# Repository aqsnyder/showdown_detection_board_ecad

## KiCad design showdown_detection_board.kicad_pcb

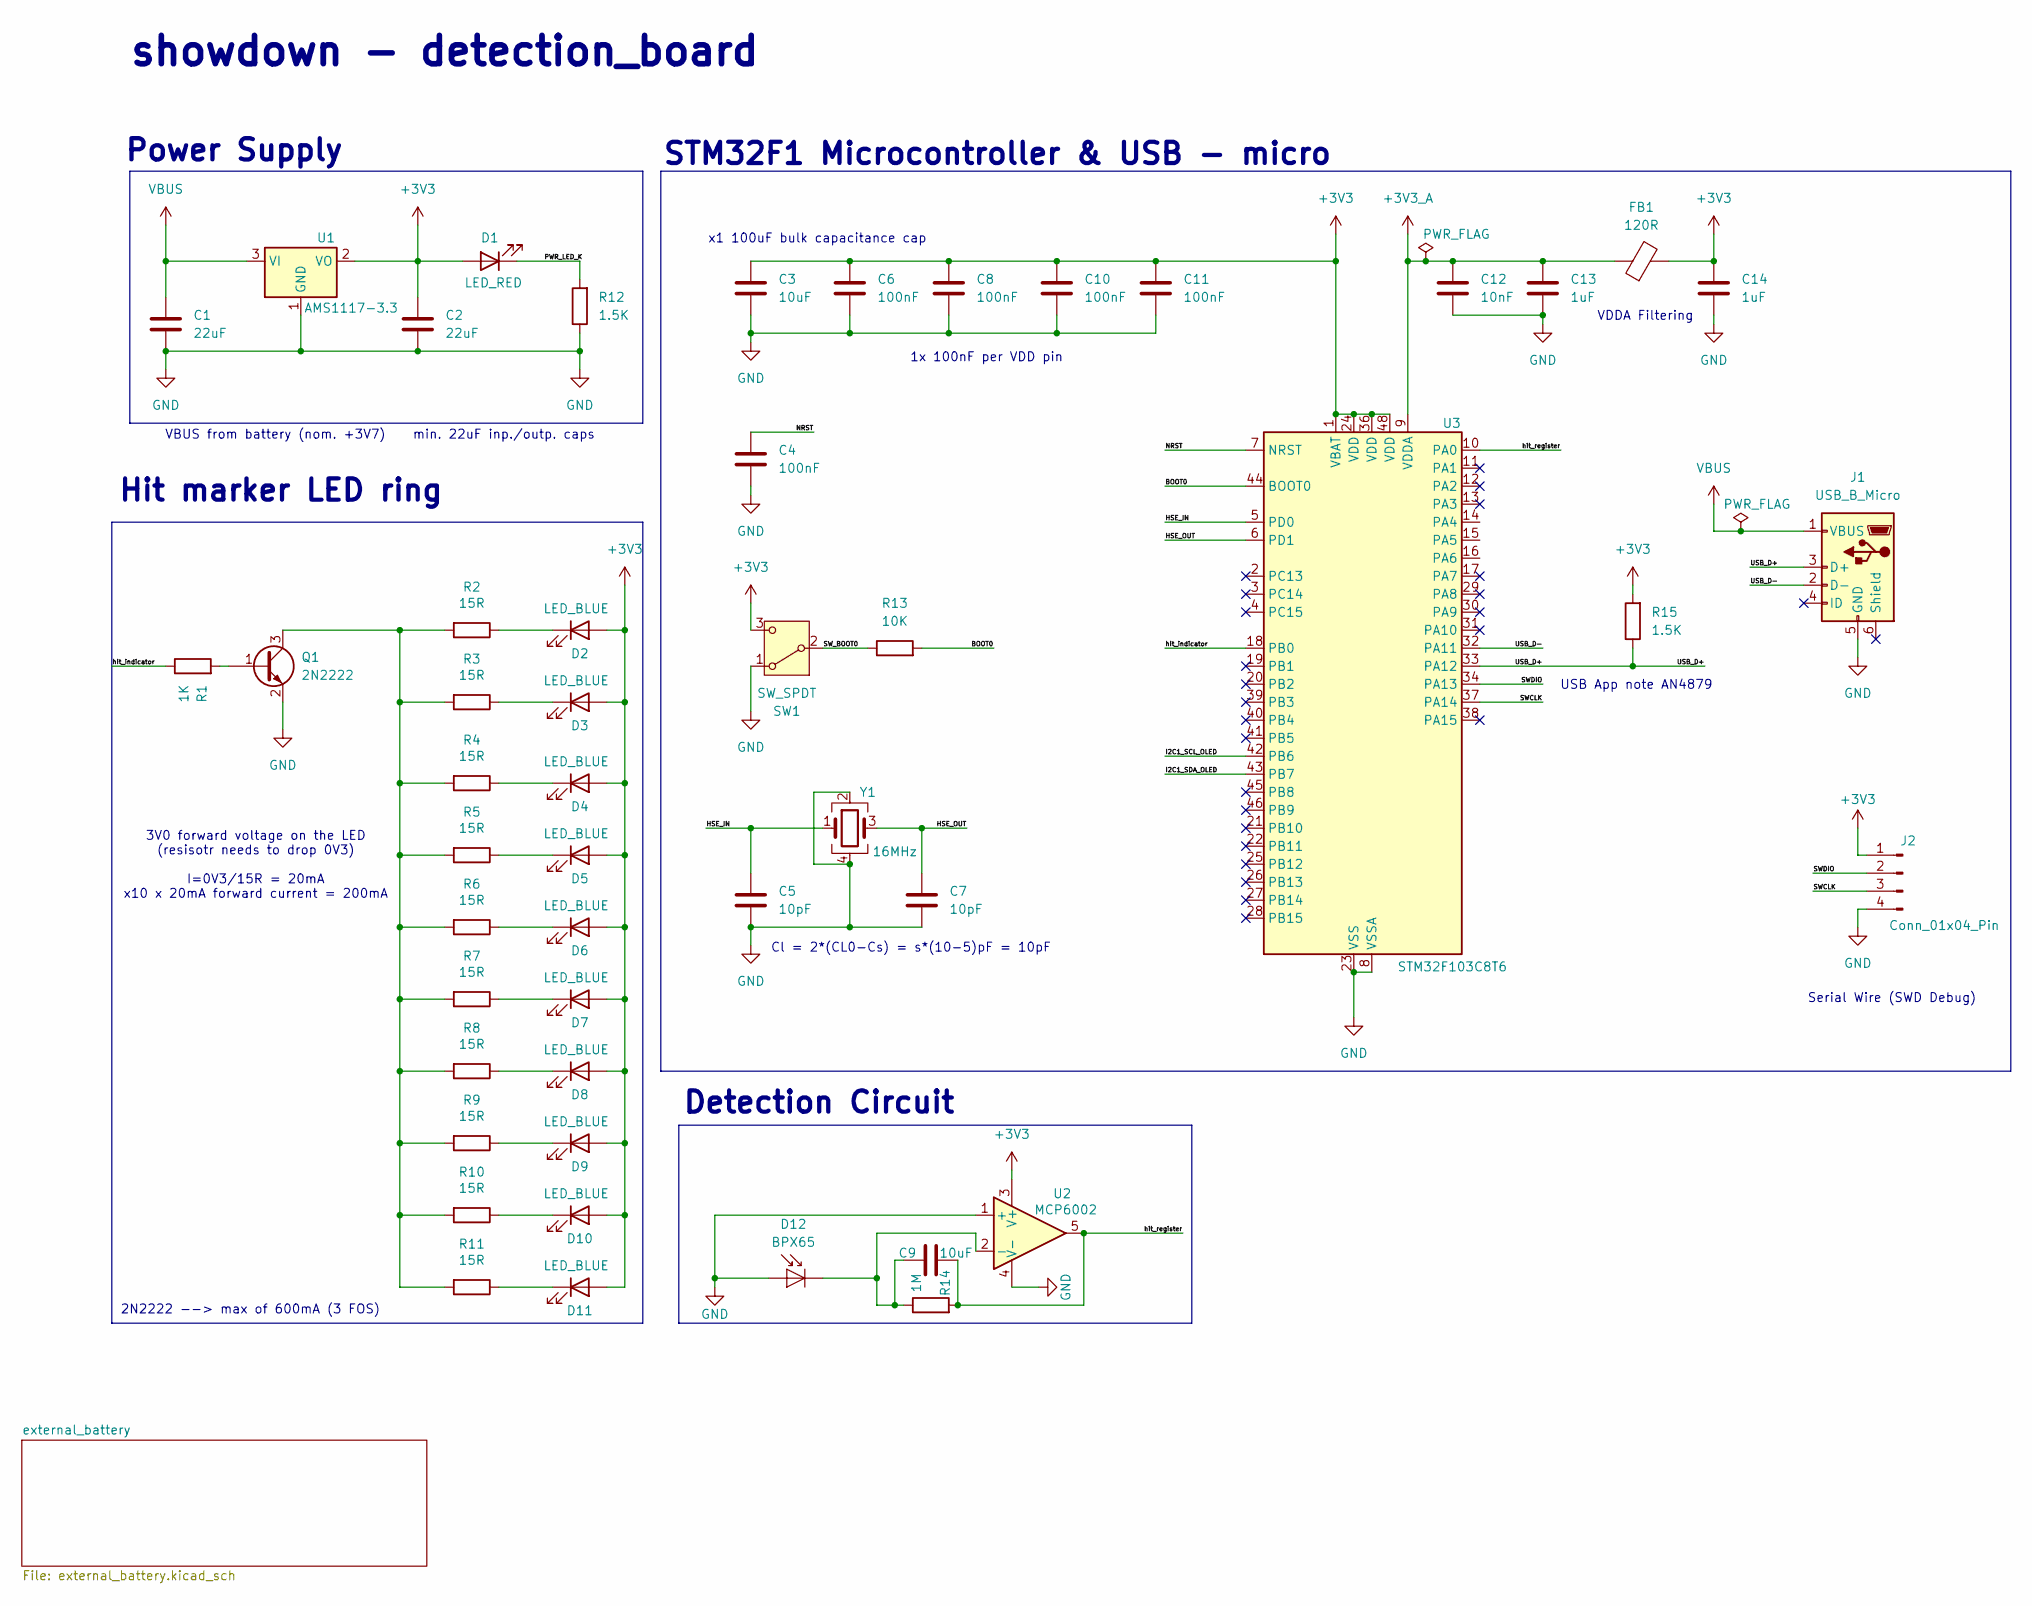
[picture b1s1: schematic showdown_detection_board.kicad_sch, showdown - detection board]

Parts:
C1, C2: 22uF; C_0603_1608Metric
C3, C9: 10uF; C_0603_1608Metric
C4, C6, C8, C10, C11: 100nF; C_0603_1608Metric
C5, C7: 10pF; C_0603_1608Metric
C12: 10nF; C_0603_1608Metric
C13, C14: 1uF; C_0603_1608Metric
D1: LED_RED; LED_0805_2012Metric
D2, D3, D4, D5, D6, D7, D8, D9, D10, D11: LED_BLUE; LED_0805_2012Metric
D12: BPX65; TO-18-2_Lens
FB1: 120R; L_0603_1608Metric
J1: USB_B_Micro; USB_Micro-AB_Molex_47590-0001
J2: Conn_01x04_Pin; PinHeader_1x04_P2.54mm_Horizontal
Q1: 2N2222; TO-92
R1: 1K; R_0603_1608Metric
R2, R3, R4, R5, R6, R7, R8, R9, R10, R11: 15R; R_0603_1608Metric
R12, R15: 1.5K; R_0603_1608Metric
R13: 10K; R_0603_1608Metric
R14: 1M; R_0603_1608Metric
SW1: SW_SPDT; SW_Slide-03_Wuerth-WS-SLTV_10x2.5x6.4_P2.54mm
U1: AMS1117-3.3; SOT-223-3_TabPin2
U2: MCP6002; TDFN-8-1EP_3x2mm_P0.5mm_EP1.3x1.4mm
U3: STM32F103C8T6; LQFP-48_7x7mm_P0.5mm
Y1: 16MHz; Crystal_SMD_3225-4Pin_3.2x2.5mm

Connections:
+3V3: C2.1, C3.1, C6.1, C8.1, C10.1, C11.1, C14.1, D1.2 (A), D2.2 (A), D3.2 (A), D4.2 (A), D5.2 (A), D6.2 (A), D7.2 (A), D8.2 (A), D9.2 (A), D10.2 (A), D11.2 (A), FB1.2, J2.1, R15.2, SW1.3 (C), U1.2 (VO), U2.3 (V+), U3.1 (VBAT), U3.24 (VDD), U3.36 (VDD), U3.48 (VDD)
+3V3_A: C12.1, C13.1, FB1.1, U3.9 (VDDA)
/BOOT0: R13.2, U3.44 (BOOT0)
/HSE_IN: C5.1, U3.5 (PD0), Y1.1
/HSE_OUT: C7.1, U3.6 (PD1), Y1.3
/I2C1_SCL_OLED: U3.42 (PB6)
/I2C1_SDA_OLED: U3.43 (PB7)
/NRST: C4.1, U3.7 (NRST)
/PWR_LED_K: D1.1 (K), R12.2
/SWCLK: J2.3, U3.37 (PA14)
/SWDIO: J2.2, U3.34 (PA13)
/SW_BOOT0: R13.1, SW1.2 (B)
/USB_D+: J1.3 (D+), R15.1, U3.33 (PA12)
/USB_D-: J1.2 (D-), U3.32 (PA11)
/hit_indicator: R1.1, U3.18 (PB0)
/hit_register: C9.1, R14.2, U2.5, U3.10 (PA0)
GND: C1.2, C2.2, C3.2, C4.2, C5.2, C6.2, C7.2, C8.2, C10.2, C11.2, C12.2, C13.2, C14.2, D12.2 (A), J1.5 (GND), J2.4, Q1.2 (E), R12.1, SW1.1 (A), U1.1 (GND), U2.1 (+), U2.4 (V-), U3.8 (VSSA), U3.23 (VSS), U3.35 (VSS), U3.47 (VSS), Y1.2, Y1.4; also elsewhere on the board
unnamed: D2.1 (K), R2.1
unnamed: D3.1 (K), R3.1
unnamed: D4.1 (K), R4.1
unnamed: D5.1 (K), R5.1
unnamed: D6.1 (K), R6.1
unnamed: D7.1 (K), R7.1
unnamed: D8.1 (K), R8.1
unnamed: D9.1 (K), R9.1
unnamed: D10.1 (K), R10.1
unnamed: D11.1 (K), R11.1
unnamed: C9.2, D12.1 (K), R14.1, U2.2 (-)
unnamed: Q1.1 (B), R1.2
unnamed: Q1.3 (C), R2.2, R3.2, R4.2, R5.2, R6.2, R7.2, R8.2, R9.2, R10.2, R11.2
VBUS: C1.1, J1.1 (VBUS), U1.3 (VI); also elsewhere on the board

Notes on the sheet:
2N2222 --> max of 600mA (3 FOS)
VBUS from battery (nom. +3V7) min. 22uF inp./outp. caps
Hit marker LED ring
Cl = 2*(CL0-Cs) = s*(10-5)pF = 10pF
x1 100uF bulk capacitance cap
VDDA Filtering
Serial Wire (SWD Debug)
showdown - detection_board
Power Supply
1x 100nF per VDD pin
3V0 forward voltage on the LED (resisotr needs to drop 0V3) I=0V3/15R = 20mA x10 x 20mA forward current = 200mA
STM32F1 Microcontroller & USB - micro
Detection Circuit
USB App note AN4879

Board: 2 copper layers, 52 parts (0 on the bottom side), 29 nets, no tracks yet.

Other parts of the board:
BT2: 2460; BAT_2460
C16: 10uF; C_0603_1608Metric

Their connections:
GND: BT2.N, C16.2; also elsewhere on the board
VBUS: BT2.P, C16.1; also elsewhere on the board

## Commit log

2024-10-17 init commit
2024-10-17 most of schematic is complete
2024-10-18 started working on battery cir.
